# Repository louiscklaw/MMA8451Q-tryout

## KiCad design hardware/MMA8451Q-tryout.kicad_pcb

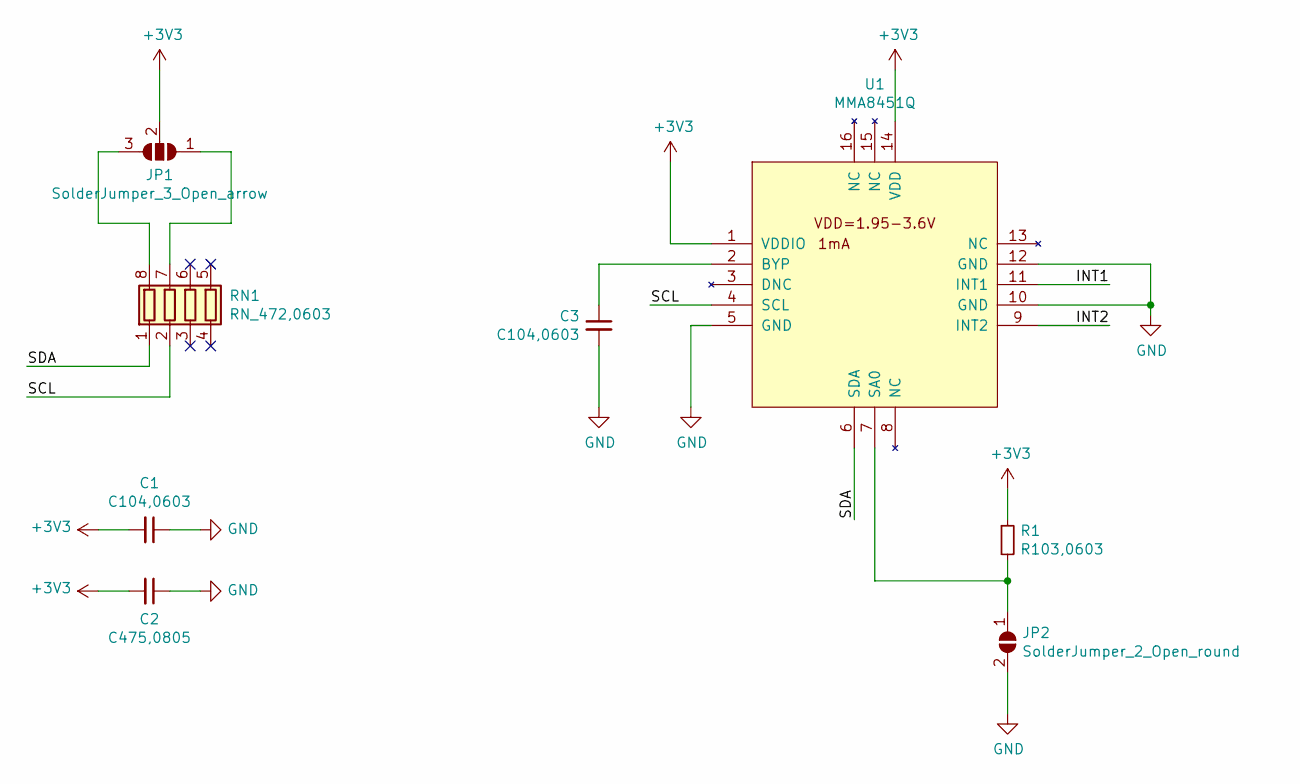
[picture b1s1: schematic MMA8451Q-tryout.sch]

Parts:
C1, C3: C104,0603; C_0603_1608Metric_Pad1.05x0.95mm_HandSolder
C2: C475,0805; C_0805_2012Metric_Pad1.15x1.40mm_HandSolder
JP1: SolderJumper_3_Open_arrow; SolderJumper-3_P2.0mm_Open_TrianglePad1.0x1.5mm_NumberLabels
JP2: SolderJumper_2_Open_round; SolderJumper-2_P1.3mm_Open_RoundedPad1.0x1.5mm
R1: R103,0603; R_0603_1608Metric_Pad1.05x0.95mm_HandSolder
RN1: RN_472,0603; R_Array_Concave_4x0603
U1: MMA8451Q; MMA8451Q_QFN16

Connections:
+3V3: C1.2, C2.2, JP1.2 (C), R1.1, U1.1 (VDDIO), U1.14 (VDD)
/INT1: U1.11 (INT1)
/INT2: U1.9 (INT2)
/SCL: RN1.2 (R2.1), U1.4 (SCL)
/SDA: RN1.1 (R1.1), U1.6 (SDA)
GND: C1.1, C2.1, C3.2, JP2.2 (B), U1.5 (GND), U1.10 (GND), U1.12 (GND)
unnamed: C3.1, U1.2 (BYP)
unnamed: JP1.1 (A), RN1.7 (R2.2)
unnamed: JP1.3 (B), RN1.8 (R1.2)
unnamed: JP2.1 (A), R1.2, U1.7 (SA0)

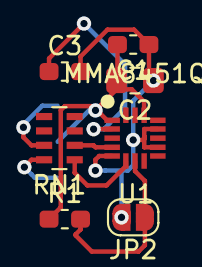
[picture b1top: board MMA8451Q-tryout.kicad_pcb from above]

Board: 2 copper layers, 8 parts (1 on the bottom side), 8 nets.

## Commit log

2019-06-12 update,
2020-05-06 ci: init travis token,
2020-05-06 ci: init travis build config,
